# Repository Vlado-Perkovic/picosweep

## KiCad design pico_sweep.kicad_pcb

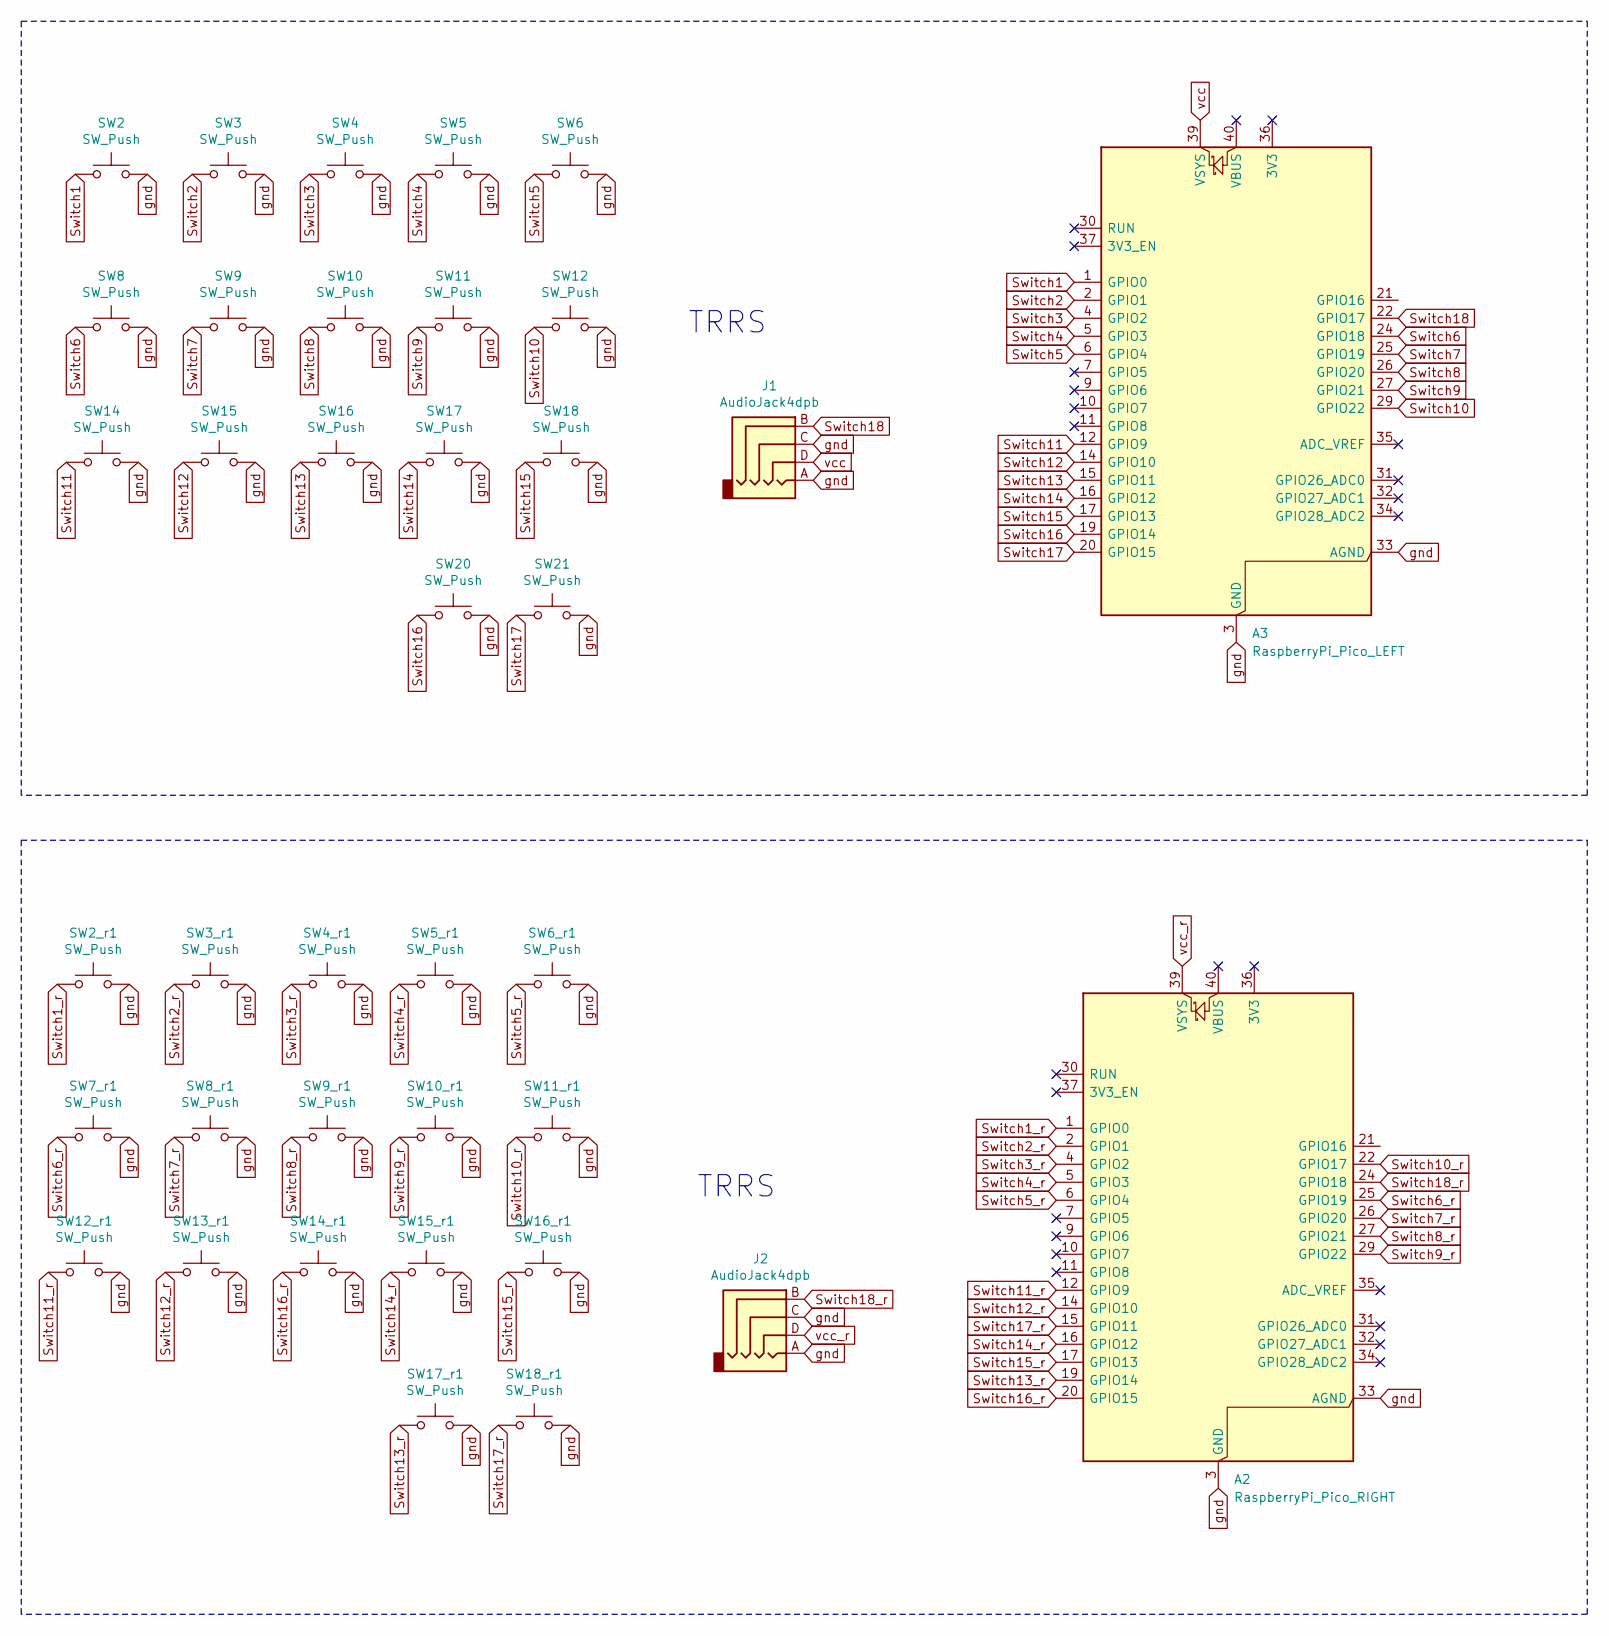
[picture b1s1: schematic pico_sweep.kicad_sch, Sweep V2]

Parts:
A2: RaspberryPi_Pico_RIGHT; RaspberryPi_Pico_Common_THT
A3: RaspberryPi_Pico_LEFT; RaspberryPi_Pico_Common_THT
J1, J2: AudioJack4dpb; MJ-4PP-9
SW2, SW2_r1, SW3, SW3_r1, SW4, SW4_r1, SW5, SW5_r1, SW6, SW6_r1, SW7_r1, SW8, SW8_r1, SW9, SW9_r1, SW10, SW10_r1, SW11, SW11_r1, SW12, SW12_r1, SW13_r1, SW14, SW14_r1, SW15, SW15_r1, SW16, SW16_r1, SW17, SW17_r1, SW18, SW18_r1, SW20, SW21: SW_Push; choc-v1-with-millmax

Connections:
Switch1: A3.1 (GPIO0), SW2.1
Switch1_r: A2.1 (GPIO0), SW2_r1.1
Switch2: A3.2 (GPIO1), SW3.1
Switch2_r: A2.2 (GPIO1), SW3_r1.1
Switch3: A3.4 (GPIO2), SW4.1
Switch3_r: A2.4 (GPIO2), SW4_r1.1
Switch4: A3.5 (GPIO3), SW5.1
Switch4_r: A2.5 (GPIO3), SW5_r1.1
Switch5: A3.6 (GPIO4), SW6.1
Switch5_r: A2.6 (GPIO4), SW6_r1.1
Switch6: A3.24 (GPIO18), SW8.1
Switch6_r: A2.25 (GPIO19), SW7_r1.1
Switch7: A3.25 (GPIO19), SW9.1
Switch7_r: A2.26 (GPIO20), SW8_r1.1
Switch8: A3.26 (GPIO20), SW10.1
Switch8_r: A2.27 (GPIO21), SW9_r1.1
Switch9: A3.27 (GPIO21), SW11.1
Switch9_r: A2.29 (GPIO22), SW10_r1.1
Switch10: A3.29 (GPIO22), SW12.1
Switch10_r: A2.22 (GPIO17), SW11_r1.1
Switch11: A3.12 (GPIO9), SW14.1
Switch11_r: A2.12 (GPIO9), SW12_r1.1
Switch12: A3.14 (GPIO10), SW15.1
Switch12_r: A2.14 (GPIO10), SW13_r1.1
Switch13: A3.15 (GPIO11), SW16.1
Switch13_r: A2.19 (GPIO14), SW17_r1.1
Switch14: A3.16 (GPIO12), SW17.1
Switch14_r: A2.16 (GPIO12), SW15_r1.1
Switch15: A3.17 (GPIO13), SW18.1
Switch15_r: A2.17 (GPIO13), SW16_r1.1
Switch16: A3.19 (GPIO14), SW20.1
Switch16_r: A2.20 (GPIO15), SW14_r1.1
Switch17: A3.20 (GPIO15), SW21.1
Switch17_r: A2.15 (GPIO11), SW18_r1.1
Switch18: A3.22 (GPIO17), J1.B
Switch18_r: A2.24 (GPIO18), J2.B
gnd: A2.3 (GND), A2.8 (GND), A2.13 (GND), A2.18 (GND), A2.23 (GND), A2.28 (GND), A2.33 (AGND), A2.38 (GND), A3.3 (GND), A3.8 (GND), A3.13 (GND), A3.18 (GND), A3.23 (GND), A3.28 (GND), A3.33 (AGND), A3.38 (GND), J1.A, J1.C, J2.A, J2.C, SW2.2, SW2_r1.2, SW3.2, SW3_r1.2, SW4.2, SW4_r1.2, SW5.2, SW5_r1.2, SW6.2, SW6_r1.2, SW7_r1.2, SW8.2, SW8_r1.2, SW9.2, SW9_r1.2, SW10.2, SW10_r1.2, SW11.2, SW11_r1.2, SW12.2, SW12_r1.2, SW13_r1.2, SW14.2, SW14_r1.2, SW15.2, SW15_r1.2, SW16.2, SW16_r1.2, SW17.2, SW17_r1.2, SW18.2, SW18_r1.2, SW20.2, SW21.2
vcc: A3.39 (VSYS), J1.D
vcc_r: A2.39 (VSYS), J2.D

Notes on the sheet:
TRRS

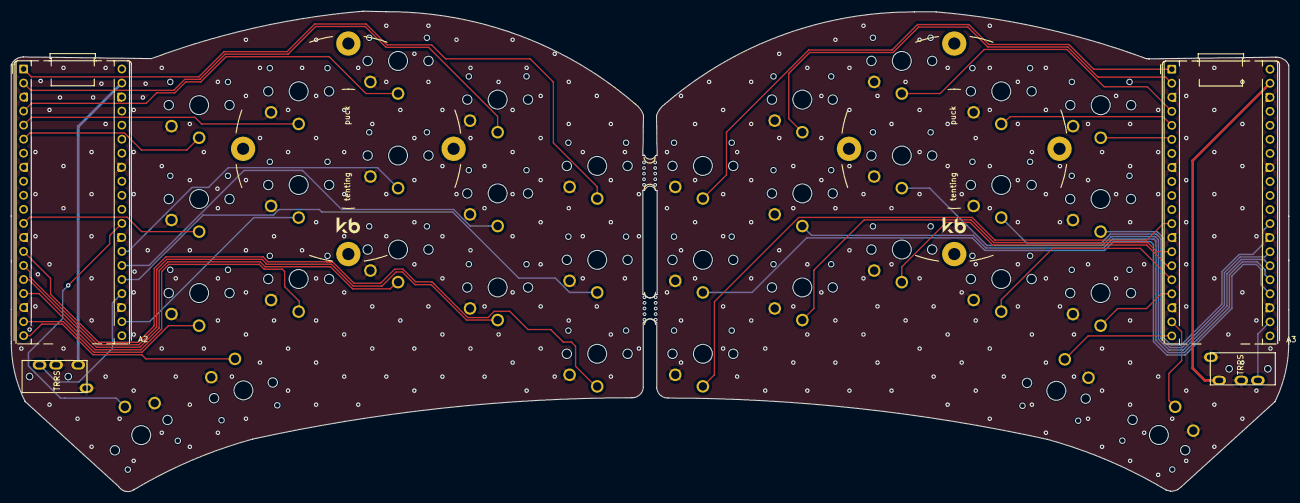
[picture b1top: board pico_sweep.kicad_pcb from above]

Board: 2 copper layers, 231.2 x 86.9 mm, 40 parts (1 on the bottom side), 39 nets.

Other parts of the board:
mouse-bite-2mm-slot, mouse-bite-2mm-slot#2: VAL**; mouse-bite-5mm-slot-with-space-for-track

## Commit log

2026-02-01 add .gitignore
2026-02-01 .gitignore
2026-02-01 add v0.1
